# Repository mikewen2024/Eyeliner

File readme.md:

# Eyeliner — Melty-Brain Combat Robot

A 1lb (antweight) melty-brain combat robot. A melty-brain spins the entire chassis at 1,000–2,000 RPM while pulsing drive motors ~100 times/second to achieve controlled translational movement — maximum hitting power, and one of the hardest archetypes to execute correctly.

**Key system requirements:** MHz-range onboard MCU, high-range accelerometer (~400g) for RPM/heading, per-motor drive current of ~30A (≈500W), and all electronics surviving constant 200–300g with peak impact accelerations orders of magnitude higher.

To read more about the development of the project and past versions, check out my personal technical blog [here](https://future-wool-0d5.notion.site/Eyeliner-Melty-brain-Combat-Robot-2ede4d628bf380b29920f43a3518d5c0) :)

---

## Current Iteration

**Hardware:** XIAO ESP32-S3 PLUS MCU, LSM6DSV320X IMU, Repeat Robotics BEC, ELRS nano receiver, dual 35A ESCs, ws2812b LED strip, Standalone ADXL-375 Accelerometer

**Key Features:**

- Extensive consideration for signal integrity, decoupling and bulk capacitance, and transients protection on all vulnerable MCU GPIO ports
- Made to run on 4s-6s LiHV with minimal changes (TVS diode change), interface with a range of possible sensors, and run interchangeably with antweight and beetleweight electronics
- Interchangeable high-kv 2207 "pacer" motors (outright top-range hitting power) and low-kv 2822 motors (faster spin-up with less current draw)
- LSM6DSV320X IMU with high and low range readout registers, built-in impact detection and interrupt capability, SPI interface 
- Custom UART interface for ELRS receiver to improve signal stability and expand channel bandwidth to 16 channels 
- LED strips for better heading and state indication
- Spare set of SPI connections for standalone ADXL375 or other sensors
- Shock isolated mounting with bracing for connectors
- Judicious ground plane placement for good return paths and receiver signal integrity, high-speed trace routing to reduce cross-talk and RC-loss, balancing current surge protection and voltage surge protection with TVS Diodes
- Up to 2500W burst capacity on HV side via solder busses, structural stability via extensive via stitching
- Spare GPIO connections for thermistors, IR sensors, etc...
- DSHOT600 and DSHOT1200 for high rate and accurate motor torque control at speed, built-in twisted-pairs for signal lines with GND return paths as close as possible to ESC grounds

**Upcoming Changes:** 

- Dual H3LIS331DL accelerometers (rotational speed without knowing center of rotation), easier-to-solder footprint
- More robust LDO system for 5V side
- Precharge circuit for higher-voltage inputs
- Two-way DSHOT for traction control
- Easily-removable high-speed connectors for ESCs
- Switch to STM32 for higher clock speeds, ESP32 for telemetry and LED control only
- Custom sensored ESCs
- Custom BMS

---

### Byeliner — Beetleweight Upscale V0 *(March 2026 – Present)*
**Class:** 3lb (beetleweight)
**Hardware Changes:** Oversize 790 kV 3548 motors, dual 80A 8s-capable VORTEX F65 ESCs, dual 4s LiHV batteries

A 3lb version ("Byeliner") built for **Robobrawl**, early April 2026. The chassis is a rigid CURV and aluminum skeleton wrapped in TPU. On the code side, we are also moving towards platformIO for more organized operation.

---

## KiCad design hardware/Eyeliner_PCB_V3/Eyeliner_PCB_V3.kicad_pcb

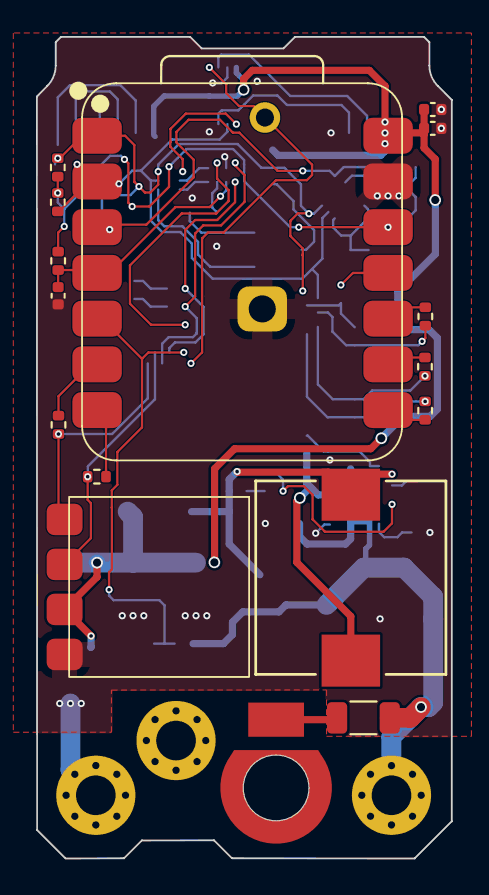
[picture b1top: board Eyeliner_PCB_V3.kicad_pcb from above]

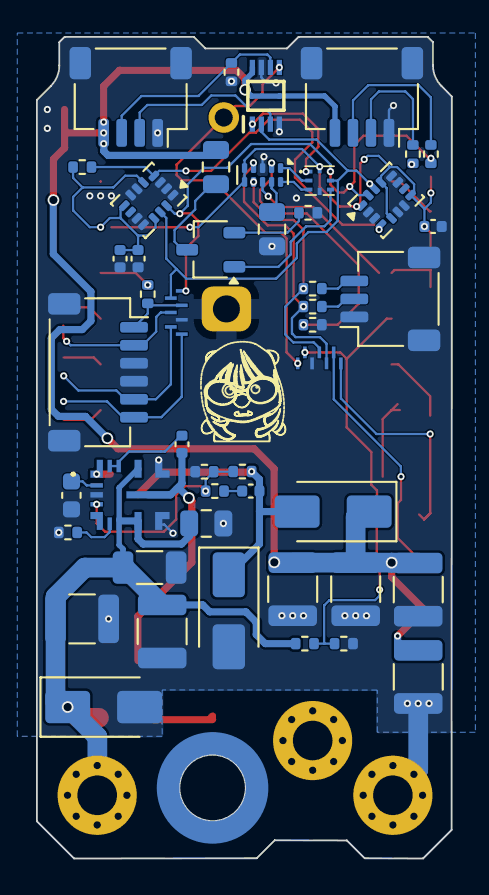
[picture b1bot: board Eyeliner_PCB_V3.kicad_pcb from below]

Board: 2 copper layers, 23.0 x 45.6 mm, 67 parts (47 on the bottom side), 48 nets.

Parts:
Batt1: VBat; MountingHole_2.2mm_M2_Pad_Via
C1: C0603X5R500-105KNP-CT; C_0603_1608Metric
C2: GMC21X7R104K35NT; C_0805_2012Metric
C3, C5, C11, C12, C16, C17: MSASG32MSB5226MPNA01; C_1210_3225Metric
C4: GCJ31CR71H225KA12L; C_1206_3216Metric
C6: 470nF; C_0402_1005Metric
C7, C9: 100nF; C_0402_1005Metric
C8, C14, C15: 100 nF; C_0402_1005Metric
C10: 16pF; C_0402_1005Metric
C13: 1uF; C_0402_1005Metric
Conn_LEDs1: JST_SH_01x04; JST_SH_SM04B-SRSS-TB_1x04-1MP_P1.00mm_Horizontal
D1: SMAJ30A or SMAJ24A; D_SMA
D2: SMAJ6.0A; D_SMA
D3: STPS2L30A; D_SMA
ESCs1: JST_SH_01x06; JST_SH_SM06B-SRSS-TB_1x06-1MP_P1.00mm_Horizontal
GND1: GND_ESCs; MountingHole_2.2mm_M2_Pad_Via
HV1: HV_ESCs; MountingHole_2.2mm_M2_Pad_Via
I2C1: JST_SH_01x04; JST_SH_SM04B-SRSS-TB_1x04-1MP_P1.00mm_Horizontal
IC1: PCA9570GMH
IC2: 74AHCT2G125DC,125; SOP50P310X100-8N
IR1: TestPoint_2Pole; C_0805_2012Metric
J1: S7131-45R; HARWIN_S7121-42R
J2: 4871; 4871_Switch_Precharge
L1: SRP1038A-150M; IND_SRP1038A_BRN
Q1: BSS138; TSOT-23
R1, R19: 4.7k; R_0402_1005Metric
R2, R3, R5, R15, R16, R17, R18, R20, R21, R22, R23: 100; R_0402_1005Metric
R4: 30k; R_0402_1005Metric
R6: RC1206FR-07100RL; R_1206_3216Metric
R7, R11: 20k; R_0402_1005Metric
R8: 5.1k; R_0402_1005Metric
R9, R10, R13, R14: 1k; R_0402_1005Metric
R12: 2k; R_0402_1005Metric
R24: 10k; R_0402_1005Metric
RTD_Onboard1: TestPoint_2Pole; C_0805_2012Metric
Receiver1: BetaFPV ELRS Lite
Temps1: JST_SH_01x03; JST_SH_SM03B-SRSS-TB_1x03-1MP_P1.00mm_Horizontal
U1: LM61440AANRJRR; LM61440AASQRJRRQ1
U2: XIAO-ESP32-S3-SMD
U3, U4: LSM6DSV320XTR; LGA-14_3x2.5mm_P0.5mm_LayoutBorder3x4y
U5: TMUX1204DQAR; USON-10_2.5x1.0mm_P0.5mm
U6, U7: RCLAMP3346P.TNT; SGP2708N7_SEM

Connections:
/Top_Board/Bias: C10.1, D2.1 (K), D3.2 (A), L1.2, R7.2, U1.1 (BIAS_1), U1.15 (BIAS_2)
/Top_Board/Dshot1: R23.2, U2.9 (D8)
/Top_Board/Dshot1_Proc: ESCs1.5, R23.1, U7.7
/Top_Board/Dshot2: R21.2, U2.10 (D9)
/Top_Board/Dshot2_Proc: ESCs1.2, R21.1, U7.6
/Top_Board/ESC_Telem1: R22.2, U2.8 (D7)
/Top_Board/ESC_Telem1_Proc: ESCs1.6, R22.1, U7.1
/Top_Board/ESC_Telem2: R20.2, U2.11 (D10)
/Top_Board/ESC_Telem2_Proc: ESCs1.1, R20.1, U7.3
/Top_Board/FB: R7.1, R8.2, R9.2, U1.4 (FB)
/Top_Board/INT: R1.1, U2.3 (D2), U3.4 (INT1), U4.4 (INT1)
/Top_Board/LEDs: IC2.5 (2A), U2.16 (MTDO), U6.1
/Top_Board/LEDs_EN: IC1.1 (P0), IC2.1 (~1OE)
/Top_Board/NC_1: U1.5 (PGOOD_1), U1.16 (PGOOD_2)
/Top_Board/Receiver_RX: R3.1, Receiver1.1 (RX), U6.4
/Top_Board/Receiver_TX: R2.2, Receiver1.2 (TX), U6.5
/Top_Board/SCL: IC1.6 (SCL), IC2.2 (1A), R10.1, R15.1, U2.2 (D1), U3.13 (SCL), U4.13 (SCL), U7.5
/Top_Board/SDA: IC1.7 (SDA), R13.1, R16.2, U2.1 (D0), U3.14 (SDA), U4.14 (SDA), U7.4
/Top_Board/Sense: C15.1, R14.1, U2.4 (D3), U5.8 (D)
/Top_Board/Temp1_1: R18.2, U5.7 (S4), U6.6
/Top_Board/Temp2_1: R17.2, U5.4 (S3), U6.3
/Top_Board/TempRef_1: R19.2, U5.2 (S1)
/Top_Board/Temp_Sel1: IC1.2 (P1), U5.1 (A0)
/Top_Board/Temp_Sel2: IC1.3 (P2), U5.10 (A1)
/Top_Board/Vbat_Sense: R11.1, R12.2, U2.5 (D4), U6.7
GND: C1.1, C2.2, C3.2, C4.2, C5.2, C6.2, C8.2, C9.2, C11.2, C12.2, C13.2, C14.2, C15.2, C16.2, C17.2, Conn_LEDs1.1, Conn_LEDs1.MP, D1.2 (A), D2.2 (A), ESCs1.3, ESCs1.4, ESCs1.MP, GND1.1 (1_1), I2C1.1, I2C1.MP, IC1.4 (VSS), IC2.4 (GND), IC2.7 (~2OE), R4.1, R5.1, R8.1, R12.1, R19.1, R24.1, RTD_Onboard1.2, Receiver1.4 (GND), Temps1.1, Temps1.MP, U1.3 (AGND), U1.9 (PGND1_1), U1.11 (PGND2_1), U1.17 (PGND1_2), U1.18 (PGND2_2), U2.13 (GND), U2.25 (PAD), U3.2 (SDX), U3.3 (SCX), U3.6 (GND), U3.7 (GND), U3.10 (OCS_AUX), U3.11 (SDO_AUX), U4.1 (SDO/TA0), U4.2 (SDX), U4.3 (SCX), U4.6 (GND), U4.7 (GND), U4.10 (OCS_AUX), U4.11 (SDO_AUX), U5.3 (GND), U6.2, U7.2
unnamed: C10.2, R9.1
unnamed: Conn_LEDs1.2, IC2.3 (2Y)
unnamed: Conn_LEDs1.3, IC2.6 (1Y), R24.2
unnamed: I2C1.2, R15.2
unnamed: I2C1.3, R16.1
unnamed: IC1.5 (P3), Q1.1 (G)
unnamed: J1.SH1 (SHIELD_SH1), R6.2
unnamed: Batt1.1 (1_1), J2.2 (Ext)
unnamed: IR1.2, Q1.3 (D)
unnamed: Q1.2 (S), R5.2
unnamed: R17.1, Temps1.2
unnamed: R18.1, Temps1.3
unnamed: C7.2, U1.13 (RBOOT), U1.14 (CBOOT)
unnamed: R4.2, U1.6 (RT)
unnamed: C7.1, L1.1, U1.10 (SW)
unnamed: C1.2, U1.2 (VCC)
unnamed: R3.2, U2.6 (D5)
unnamed: R2.1, U2.7 (D6)
unnamed: RTD_Onboard1.1, U5.9 (S2)
VCC_3V3: C6.1, C8.1, C9.1, IC1.8 (VDD), R1.2, R10.2, R13.2, R14.2, U2.12 (3V3_OUT), U3.1 (SDO/TA0), U3.5 (VDDIO), U3.8 (VDD), U3.12 (CS), U4.5 (VDDIO), U4.8 (VDD), U4.12 (CS), U5.5 (EN), U5.6 (VDD)
VCC_5V: C11.1, C12.1, C13.1, C14.1, C16.1, C17.1, Conn_LEDs1.4, D3.1 (K), I2C1.4, IC2.8 (VCC), IR1.1, Receiver1.3 (5V), U2.14 (VBUS)
VCC_HV: C2.1, C3.1, C4.1, C5.1, D1.1 (K), HV1.1 (1_1), J2.1 (In), R6.1, R11.2, U1.7 (EN/SYNC), U1.8 (VIN1), U1.12 (VIN2)

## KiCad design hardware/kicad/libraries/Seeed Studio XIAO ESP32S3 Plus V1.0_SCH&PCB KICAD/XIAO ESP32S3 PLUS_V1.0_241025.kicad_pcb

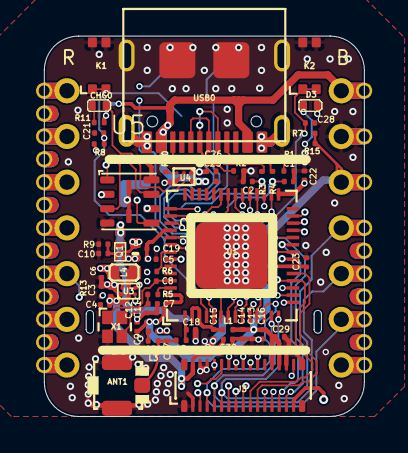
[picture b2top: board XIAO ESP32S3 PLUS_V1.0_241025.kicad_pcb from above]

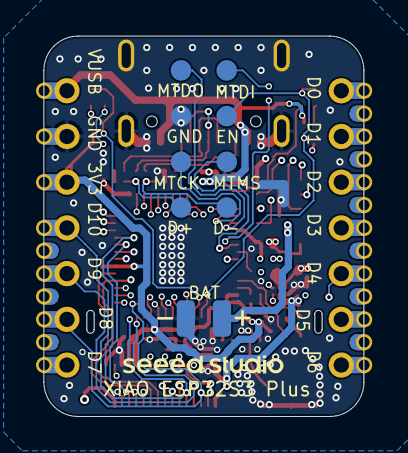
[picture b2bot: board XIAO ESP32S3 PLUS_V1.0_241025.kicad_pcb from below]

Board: 6 copper layers, 17.8 x 21.1 mm, 70 parts (10 on the bottom side), 62 nets.

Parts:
ANT1: U.FL-R-SMT-1; U-FL3P-SMD-2.6X2.6X1.0MM
BAT0: VBAT; TP-80X40MIL
C1, C2, C17, C20: DNP; C0201
C3, C9, C13, C16: 2.2uF; C0201
C4, C5, C6: 4.7uF; C0201
C7, C8, C28: 10pF; C0201
C10, C21, C25, C26: 1uF; C0201
C11, C14, C15, C19, C22, C23, C29, C30: 100nF; C0201
C12: 10nF; C0201
C18: 1pF; C0201
CHG0: RED; LED-0402
D2: LMBR4010BST5G; DFN1006-2L
D3: Yellow; LED-0402
GND0: GND; TP-80X40MIL
J3: DF40C-30DP-0.4V(51); BTB30-0.4-7.52X2.97X1.14
K1, K2: SKTAAAE010/311021459; SW4-SMD-2.8-2.6X1.6X0.53MM
L1: 2nH; L0201
L2: 3.3nH; L0201
L3: DNP; L0201
L4: 470nH; L0603
Q1: PMOS_1.00.60.35MM; PMOS_1.0*0.6*0.35MM
R1, R2: 5.1K; R0201
R3, R4: 22R; R0201
R5: 0R; R0201
R6: 499R; R0201
R7, R8, R11: 10K; R0201
R9: 100K; C0201
R10: 220K; R0201
R13: 249K; R0201
R15: 1.5K; R0201
TP1, TP2, TP3, TP4, TP5, TP6, TP7, TP8: TEST-POINT'4545'; TP-D45MIL
U1: MCU-ESP32-S3; QFN56G-0.4-7X7MM
U2: XIAO-HALF-HOLE-23P; MOUDLE23P-XIAO-HALF-HOLE
U3: PMIC-SGM6029; BGA6-0.35-0.745X10.95X0.4MM
U4: SGM40567-4.2XG/TR; WLCSP-0.4-0.92X1.16X0.4MM
U5: PY25Q128HA-DFH-IR; USON8-0.8-3X3X0.55MM
USB0: UBF31-0171; USB2.0-TYPE-C
X1: 40MHz/306011364; X4-SMD-1.6X1.2X0.35MM

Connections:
/D0/A0: U1.6 (GPIO1), U2.1 (PA02_A0_D0)
/D1/A1: U1.7 (GPIO2), U2.2 (PA4_A1_D1)
/D2/A2: J3.2, U1.8 (GPIO3), U2.3 (PA10_A2_D2)
/D3/A3: U1.9 (GPIO4), U2.4 (PA11_A3_D3)
/D4/I2C_SDA: U1.10 (GPIO5), U2.5 (PA8_A4_D4_SDA)
/D5/I2C_SCL: U1.11 (GPIO6), U2.6 (PA9_A5_D5_SCL)
/D6/TX: R6.2, U2.7 (PB08_A6_D6_TX)
/D7/RX: U1.50 (U0RXD), U2.8 (PB09_A7_D7_RX)
/D8/A8/SCK: J3.3, U1.12 (GPIO7), U2.9 (PA7_A8_D8_SCK)
/D9/A9/MISO: J3.4, U1.13 (GPIO8), U2.10 (PA5_A9_D9_MISO)
/D10/A10/MOSI: J3.5, U1.14 (GPIO9), U2.11 (PA6_A10_D10_MOSI)
/EN: C21.2, K1.1 (A0), K1.3 (A1), R8.1, TP6.T, U1.4 (CHIP_PU)
/ESP_USB_D+: C1.2, R4.2, TP8.T, U1.26 (GPIO20)
/ESP_USB_D-: C2.2, R3.2, TP7.T, U1.25 (GPIO19)
/GPIO0: C28.2, K2.1 (A0), K2.3 (A1), R7.1, U1.5 (GPIO0)
/IO10/XMCLK/ADC_BAT: J3.6, U1.15 (GPIO10), U2.20
/IO11/DVP_Y8/SPI_MOSI1: J3.7, U1.16 (GPIO11), U2.21
/IO12/DVP_Y7/SPI_MISO1: J3.8, U1.17 (GPIO12), U2.22
/IO13/DVP_PCLK/SPI_SCK1: J3.9, U1.18 (GPIO13), U2.23
/IO14/DVP_Y6: J3.10, U1.19 (GPIO14)
/IO15/DVP_Y2: J3.11, U1.21 (XTAL_32K_P)
/IO16/DVP_Y5: J3.12, U1.22 (XTAL_32K_N)
/IO17/DVP_Y3: J3.13, U1.23 (GPIO17)
/IO18/DVP_Y4: J3.14, U1.24 (GPIO18)
/IO21/USER_LED: D3.-, J3.16, U1.27 (GPIO21)
/IO38/DVP_VSYNC/I2S_SD: J3.23, U1.43 (GPIO38), U2.15
/IO47/DVP_HREF: J3.22, U1.37 (SPICLK_P)
/IO48/DVP_Y9: J3.21, U1.36 (SPICLK_N)
/MTCK/IO39/CAM_SCL/I2S_SCK: J3.24, TP5.T, U1.44 (MTCK), U2.16
/MTDI/IO41/PDM_DATA/RX1: J3.26, TP3.T, U1.47 (MTDI), U2.18
/MTDO/IO40/CAM_SDA/I2S_WS: J3.25, TP4.T, U1.45 (MTDO), U2.17
/MTMS/IO42/PDM_CLK/TX1: J3.27, TP2.T, U1.48 (MTMS), U2.19
/SPICLK: U1.33 (SPICLK), U5.6 (SCLK)
/SPICS0: U1.32 (SPICS0), U5.1 (CS#)
/SPID: U1.35 (SPID), U5.5 (SI)
/SPIHD: U1.30 (SPIHD), U5.7 (HOLD#/RESET#)
/SPIQ: U1.34 (SPIQ), U5.2 (SO)
/SPIWP: U1.31 (SPIWP), U5.3 (WP#)
/USB_D+: R4.1, USB0.A6 (A6/DP1), USB0.B6 (B6/DP2)
/USB_D-: R3.1, USB0.A7 (A7/DN1), USB0.B7 (B7/DN2)
/VBAT: BAT0.1 (T), C26.1, Q1.1 (D), U4.A1 (BAT)
/VBUS: C10.1, C25.1, D2.+, Q1.2 (G), R9.2, R11.1, U2.14 (5V), U4.A2 (VIN), USB0.A4_B9 (A4/B9/VBUS), USB0.B4_A9 (B4/A9/VBUS)
/VCC_3V3: C5.2, C6.2, C9.2, C11.2, C12.2, C13.2, C14.2, C16.2, C19.2, C23.1, C29.2, J3.18, J3.19, L1.1, L4.2, R7.2, R8.2, R15.2, U1.20 (VDD3P3_RTC), U1.46 (VDD3P3_CPU), U1.55 (VDDA@1), U1.56 (VDDA@2), U2.12 (3V3), U3.A2 (VOS)
/VDD_SPI: C22.2, U1.29 (VDD_SPI), U5.8 (VCC)
/VIN: C3.1, C4.1, C30.2, D2.-, J3.15, J3.30, Q1.3 (S), U3.B1 (VIN), U3.C2 (EN)
GND_POWER: ANT1.GND1, ANT1.GND2, C1.1, C2.1, C3.2, C4.2, C5.1, C6.1, C7.2, C8.1, C9.1, C10.2, C11.1, C12.1, C13.1, C14.1, C15.1, C16.1, C17.1, C18.1, C19.1, C20.1, C21.1, C22.1, C23.2, C25.2, C26.2, C28.1, C29.1, C30.1, GND0.1 (T), J3.1, J3.17, J3.28, J3.29, J3.31, J3.33, J3.34, K1.2 (B0), K1.4 (B1), K2.2 (B0), K2.4 (B1), R1.1, R2.2, R9.1, R10.1, R13.1, TP1.T, U1.57 (GND), U2.13 (GND), U3.A1 (GND), U4.B1 (F), U4.C2 (GND), U5.4 (GND), U5.9 (GND), U5.10 (GND), USB0.A1_B12 (A1/B12/GND), USB0.B1_A12 (B1/A12/GND), USB0.S1, USB0.S2, USB0.S3, USB0.S4, USB0.S5 (S1), USB0.S6 (S2), X1.2 (GND), X1.4 (GND@1)
unnamed: ANT1.D, C17.2, L2.1, L3.2
unnamed: C20.2, L3.1
unnamed: CHG0.+, R11.2
unnamed: D3.+, R15.1
unnamed: C18.2, L2.2, U1.1 (LNA_IN)
unnamed: R6.1, U1.49 (U0TXD)
unnamed: C15.2, L1.2, U1.2 (VDD3P3@1), U1.3 (VDD3P3@2)
unnamed: C8.2, U1.53 (XTAL_N), X1.1 (X1)
unnamed: R5.1, U1.54 (XTAL_P)
unnamed: R13.2, U3.C1 (MODE)
unnamed: L4.1, U3.B2 (SW)
unnamed: R10.2, U4.C1 (IREF)
unnamed: CHG0.-, U4.B2 (NCHG)
unnamed: R1.2, USB0.A5 (A5/CC1)
unnamed: R2.1, USB0.B5 (B5/CC2)
unnamed: C7.1, R5.2, X1.3 (X2)

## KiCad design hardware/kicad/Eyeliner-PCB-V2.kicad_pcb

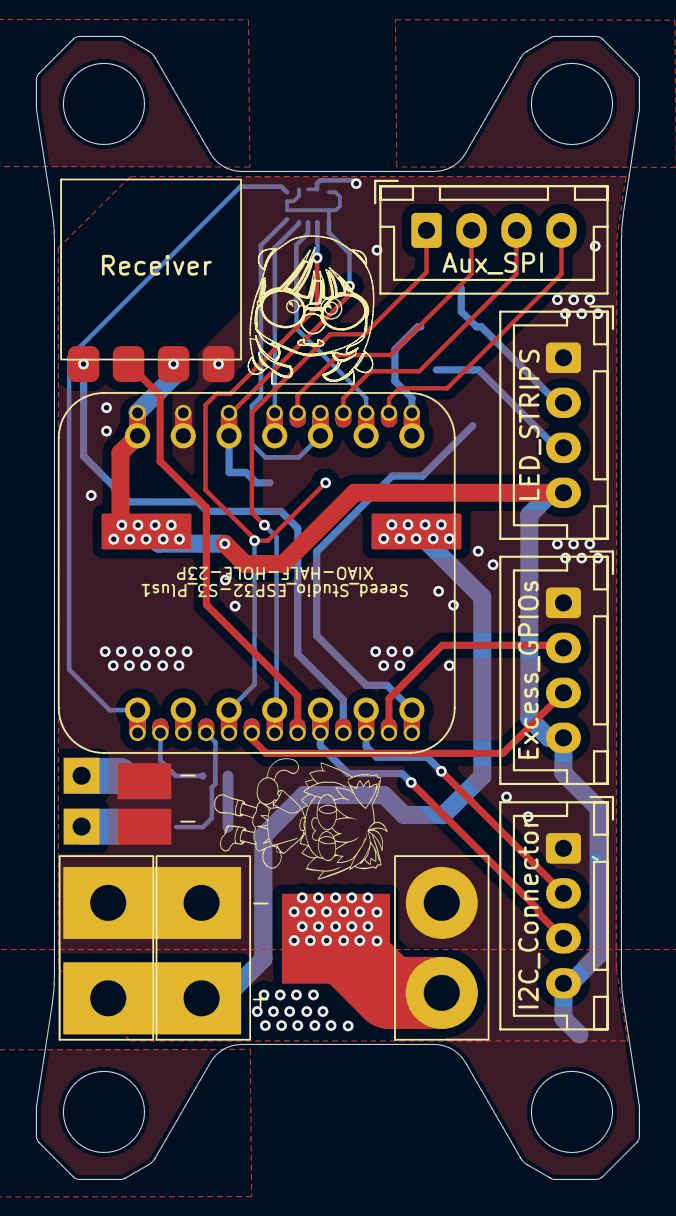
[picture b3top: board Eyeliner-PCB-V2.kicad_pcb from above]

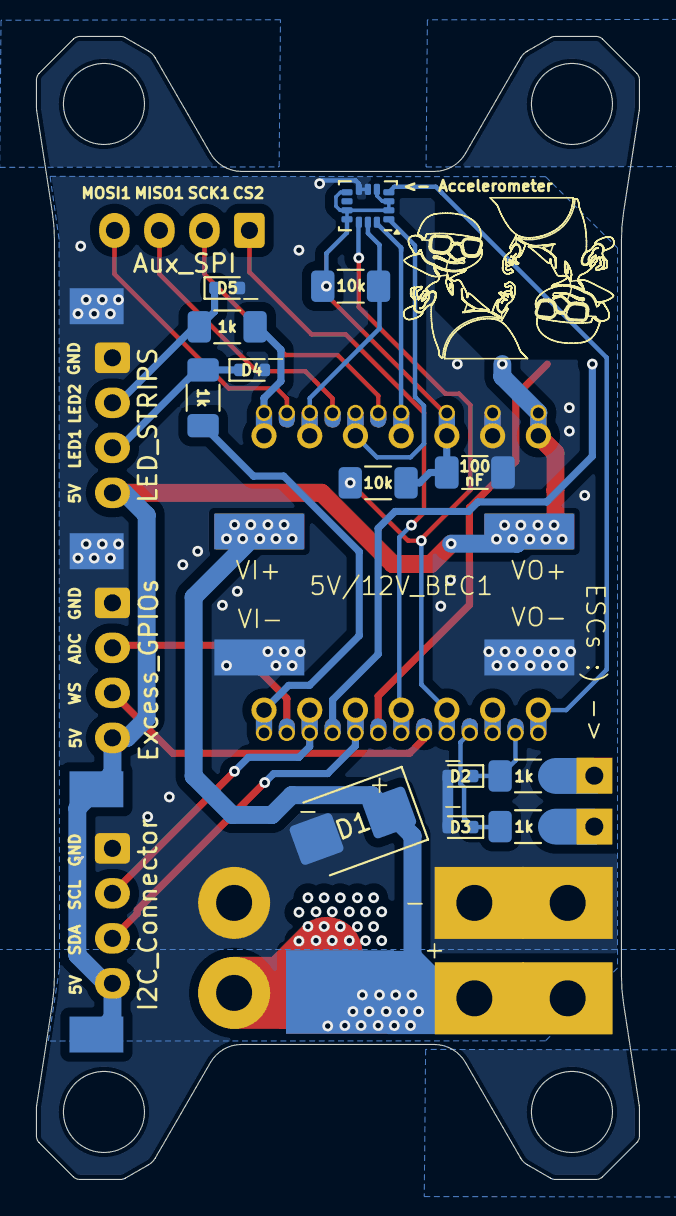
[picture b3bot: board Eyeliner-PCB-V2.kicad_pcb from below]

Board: 2 copper layers, 33.5 x 63.5 mm, 32 parts (17 on the bottom side), 28 nets.

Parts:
1k, 1k#2, 1k#3, 1k#4: 1k; R_1206_3216Metric_Pad1.30x1.75mm_HandSolder
5V/12V_BEC1: BEC_5V_12V
10k, 10k#2: 10k; R_1206_3216Metric_Pad1.30x1.75mm_HandSolder
100: 100 nF; C_1206_3216Metric_Pad1.33x1.80mm_HandSolder
+: XT-30_VERT
<- Accelerometer: LSM6DSV320XTR; LGA-14_3x2.5mm_P0.5mm_LayoutBorder3x4y
D1: D_TVS; D_SMB
D2, D3: D_TVS; D_SOD-523
D4: D_LED_1; D_SOD-523
D5: D_LED_2; D_SOD-523
ESC1, ESC2: ESC-PWM-Connection
Fingertech_Switch1: Fingertech_Switch
J1: LED_STRIPS; JST_XH_B4B-XH-A_1x04_P2.50mm_Vertical
J2: Aux_SPI; JST_XH_B4B-XH-A_1x04_P2.50mm_Vertical
J3: I2C_Connector; JST_XH_B4B-XH-A_1x04_P2.50mm_Vertical
J4: Excess_GPIOs; JST_XH_B4B-XH-A_1x04_P2.50mm_Vertical
Receiver: BetaFPV ELRS Lite
Seeed_Studio_ESP32-S3_Plus1: XIAO-HALF-HOLE-23P; MOUDLE23P-SMD-2.54-21X17.8MM.kicad_mod.kicad_sym
U1, U2, U3, U4, U5, U6: Generic_SMD_THT
XT-30_VERT1, XT-30_VERT3: XT-30_VERT

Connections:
4S_VCC: 5V/12V_BEC1.VIN+, +.VCC, D1.1 (K), Fingertech_Switch1.OUT, XT-30_VERT1.VCC
ADC_BAT: J4.2, Seeed_Studio_ESP32-S3_Plus1.20 (GPIO10_XMCLK/ADC_BAT)
CS_1: 10k.2, <- Accelerometer.12 (CS), Seeed_Studio_ESP32-S3_Plus1.3 (GPIO3_D2/A2)
CS_2: J2.1, Seeed_Studio_ESP32-S3_Plus1.4 (GPIO4_D3/A3)
ESC_1: 1k#3.2, D2.1 (K), Seeed_Studio_ESP32-S3_Plus1.15 (GPIO38_DVP_VSYNC/I2S_SD)
ESC_2: 1k.2, D3.1 (K), Seeed_Studio_ESP32-S3_Plus1.16 (GPIO39_CAM_SCL/I2S_SCK)
GND: 5V/12V_BEC1.VIN-, 5V/12V_BEC1.VO-, 100.2, +.GND, <- Accelerometer.6 (GND), <- Accelerometer.7 (GND), D1.2 (A), D2.2 (A), D3.2 (A), D4.2 (A), D5.2 (A), J1.1, J3.1, J4.1, Receiver.4 (GND), Seeed_Studio_ESP32-S3_Plus1.13 (GND), U1.1 (GND), U2.1 (GND), U3.1 (GND), U5.1 (GND), XT-30_VERT1.GND, XT-30_VERT3.GND
INT_1: <- Accelerometer.4 (INT1), Seeed_Studio_ESP32-S3_Plus1.1 (GPIO1_D0/A0)
LED_1: 1k#4.2, Seeed_Studio_ESP32-S3_Plus1.7 (U0TXD_D6/TX)
LED_2: 1k#2.2, Seeed_Studio_ESP32-S3_Plus1.8 (U0RXD_D7/RX)
MISO: <- Accelerometer.1 (SDO/TA0), Seeed_Studio_ESP32-S3_Plus1.10 (GPIO8_D9/A9/MISO)
MISO1: J2.3, Seeed_Studio_ESP32-S3_Plus1.22 (GPIO12_DVP_Y7/SPI_MISO1)
MOSI: <- Accelerometer.14 (SDA), Seeed_Studio_ESP32-S3_Plus1.11 (GPIO9_D10/A10/MOSI)
MOSI1: J2.4, Seeed_Studio_ESP32-S3_Plus1.21 (GPIO11_DVP_Y8/SPI_MOSI1)
unnamed: 1k#4.1, D4.1 (K), J1.3
unnamed: 1k#2.1, D5.1 (K), J1.2
unnamed: 1k#3.1, ESC1.1 (PWM)
unnamed: 1k.1, ESC2.1 (PWM)
Receiver_RX: Receiver.1 (RX), Seeed_Studio_ESP32-S3_Plus1.19 (GPIO42_PDM_CLK/TX1)
Receiver_TX: Receiver.2 (TX), Seeed_Studio_ESP32-S3_Plus1.18 (GPIO41_PDM_DATA/RX1)
SCK: 10k#2.2, <- Accelerometer.13 (SCL), Seeed_Studio_ESP32-S3_Plus1.9 (GPIO7_D8/A8/SCK)
SCK1: J2.2, Seeed_Studio_ESP32-S3_Plus1.23 (GPIO13_DVP_PCLK/SPI_SCK1)
SCL: J3.2, Seeed_Studio_ESP32-S3_Plus1.6 (GPIO6_D5/A5/I2C_SCL)
SDA: J3.3, Seeed_Studio_ESP32-S3_Plus1.5 (GPIO5_D4/A4/I2C_SDA)
SWITCH INPUT: Fingertech_Switch1.IN, XT-30_VERT3.VCC
VCC 3V3: 10k.1, 10k#2.1, 100.1, <- Accelerometer.2 (SDX), <- Accelerometer.3 (SCX), <- Accelerometer.5 (VDDIO), <- Accelerometer.8 (VDD), <- Accelerometer.10 (OCS_AUX), <- Accelerometer.11 (SDO_AUX), Seeed_Studio_ESP32-S3_Plus1.12 (VCC_3V3)
VCC 5V: 5V/12V_BEC1.VO+, J1.4, J3.4, J4.4, Receiver.3 (5V), Seeed_Studio_ESP32-S3_Plus1.14 (VBUS), U4.1 (VCC), U6.1 (VCC)
WS: J4.3, Seeed_Studio_ESP32-S3_Plus1.17 (GPIO40_CAM_SDA/I2S_WS)

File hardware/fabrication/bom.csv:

Designator,Footprint,Quantity,Value,LCSC Part #
"+, XT-30_VERT1, XT-30_VERT3",XT-30_VERT,3,~,
100,1206,1,100 nF,
"10K, 1K",1206,2,10k,
"1K_5, 1K_4, 1K_3, 1K_2",1206,4,1k,
5V/12V_BEC1,BEC_5V_12V,1,~,
<- ACCELEROMETER,LGA-14_3x2.5mm_P0.5mm_LayoutBorder3x4y,1,LSM6DSV320XTR,
D1,D_SMB,1,D_TVS,
"D2, D3",D_SOD-523,2,D_TVS,
D4,D_SOD-523,1,D_LED_1,
D5,D_SOD-523,1,D_LED_2,
"ESC1, ESC2",ESC-PWM-Connection,2,~,
FINGERTECH_SWITCH1,Fingertech_Switch,1,~,
J1,JST_XH_B4B-XH-A_1x04_P2.50mm_Vertical,1,LED_STRIPS,
J2,JST_XH_B4B-XH-A_1x04_P2.50mm_Vertical,1,Aux_SPI,
J3,JST_XH_B4B-XH-A_1x04_P2.50mm_Vertical,1,I2C_Connector,
J4,JST_XH_B4B-XH-A_1x04_P2.50mm_Vertical,1,Excess_GPIOs,
RECEIVER,BetaFPV ELRS Lite,1,~,
SEEED_STUDIO_ESP32-S3_PLUS1,MOUDLE23P-SMD-2.54-21X17.8MM.kicad_mod.kicad_sym,1,XIAO-HALF-HOLE-23P,
"U1, U2, U3, U4, U5, U6",Generic_SMD_THT,6,~,

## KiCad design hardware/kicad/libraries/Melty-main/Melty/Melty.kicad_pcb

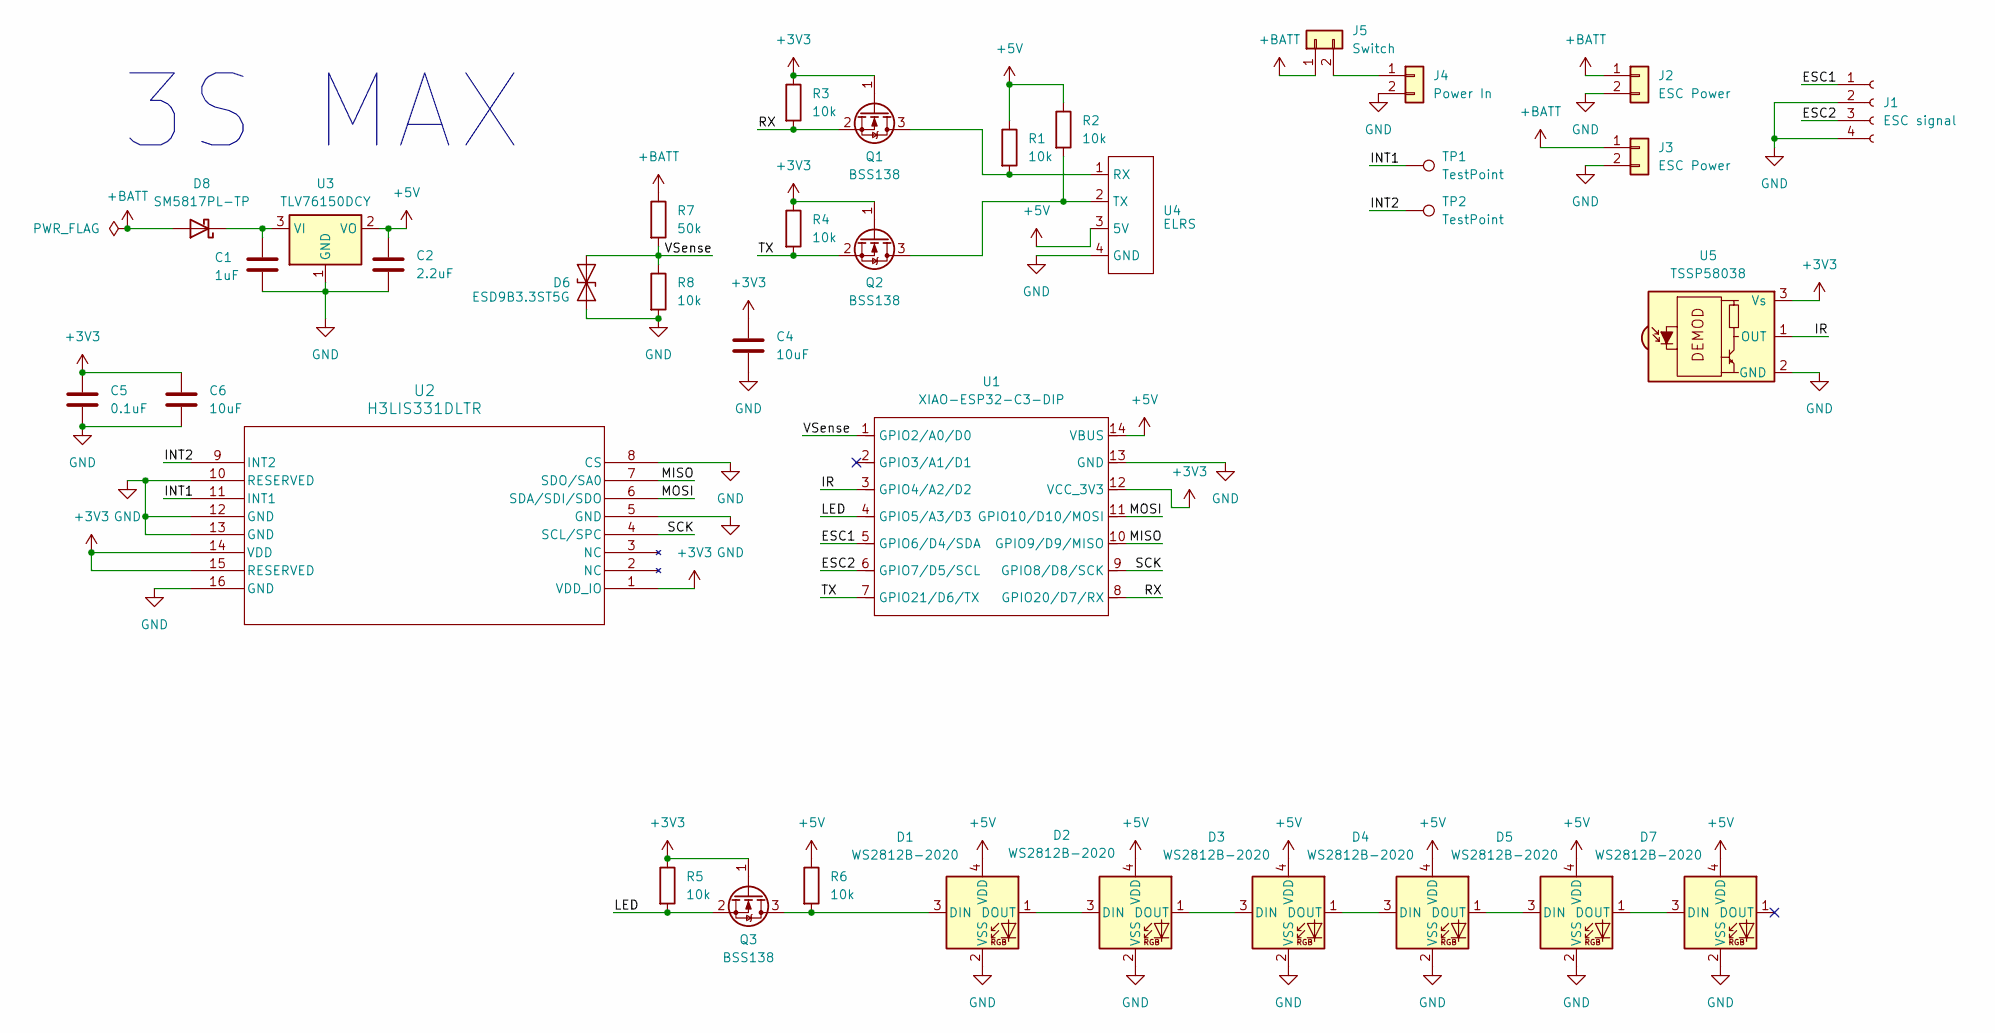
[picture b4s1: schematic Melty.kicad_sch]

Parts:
C1: 1uF; C_0603_1608Metric_Pad1.08x0.95mm_HandSolder
C2: 2.2uF; C_0603_1608Metric_Pad1.08x0.95mm_HandSolder
C4, C6: 10uF; C_0603_1608Metric_Pad1.08x0.95mm_HandSolder
C5: 0.1uF; C_0603_1608Metric_Pad1.08x0.95mm_HandSolder
D1, D2, D3, D4, D5, D7: WS2812B-2020; LED_WS2812B-2020_PLCC4_2.0x2.0mm
D6: ESD9B3.3ST5G; D_SOD-923
D8: SM5817PL-TP
J1: ESC signal; JST_GH_SM04B-GHS-TB_1x04-1MP_P1.25mm_Horizontal
J2, J3: ESC Power; PowerPADS
J4: Power In; AMASS_XT30UPB-M_1x02_P5.0mm_Vertical
J5: Switch; SwitchPads
Q1, Q2, Q3: BSS138; SOT-23
R1, R2, R3, R4, R5, R6, R8: 10k; C_0603_1608Metric_Pad1.08x0.95mm_HandSolder
R7: 50k; C_0603_1608Metric_Pad1.08x0.95mm_HandSolder
TP1, TP2: TestPoint; TestPoint_Pad_D1.0mm
U1: XIAO-ESP32-C3-DIP; XIAO-ESP32S3-SMD
U2: H3LIS331DLTR; QFN_31DLTR_STM
U3: TLV76150DCY; SOT-223-3_TabPin2
U4: ELRS; BetaFPV ELRS Lite
U5: TSSP58038; Vishay_MINICAST-3Pin

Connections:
+3V3: C4.1, C5.1, C6.1, Q1.1 (G), Q2.1 (G), Q3.1 (G), R3.1, R4.1, R5.1, U1.12 (VCC_3V3), U2.1 (VDD_IO), U2.14 (VDD), U2.15 (RESERVED), U5.3 (Vs)
+5V: C2.1, D1.4 (VDD), D2.4 (VDD), D3.4 (VDD), D4.4 (VDD), D5.4 (VDD), D7.4 (VDD), R1.1, R2.1, R6.1, U1.14 (VBUS), U3.2 (VO), U4.3 (5V)
/ESC1: J1.1, U1.5 (GPIO6/D4/SDA)
/ESC2: J1.3, U1.6 (GPIO7/D5/SCL)
/INT1: TP1.1, U2.11 (INT1)
/INT2: TP2.1, U2.9 (INT2)
/IR: U1.3 (GPIO4/A2/D2), U5.1 (OUT)
/LED: Q3.2 (S), R5.2, U1.4 (GPIO5/A3/D3)
/MISO: U1.10 (GPIO9/D9/MISO), U2.7 (SDO/SA0)
/MOSI: U1.11 (GPIO10/D10/MOSI), U2.6 (SDA/SDI/SDO)
/RX: Q1.2 (S), R3.2, U1.8 (GPIO20/D7/RX)
/SCK: U1.9 (GPIO8/D8/SCK), U2.4 (SCL/SPC)
/TX: Q2.2 (S), R4.2, U1.7 (GPIO21/D6/TX)
/VSense: D6.1 (A1), R7.2, R8.1, U1.1 (GPIO2/A0/D0)
GND: C1.2, C2.2, C4.2, C5.2, C6.2, D1.2 (VSS), D2.2 (VSS), D3.2 (VSS), D4.2 (VSS), D5.2 (VSS), D6.2 (A2), D7.2 (VSS), J1.2, J1.4, J2.2, J3.2, J4.2, R8.2, U1.13 (GND), U2.5 (GND), U2.8 (CS), U2.10 (RESERVED), U2.12 (GND), U2.13 (GND), U2.16 (GND), U3.1 (GND), U4.4 (GND), U5.2 (GND)
unnamed: D1.3 (DIN), Q3.3 (D), R6.2
unnamed: D1.1 (DOUT), D2.3 (DIN)
unnamed: D2.1 (DOUT), D3.3 (DIN)
unnamed: D3.1 (DOUT), D4.3 (DIN)
unnamed: D4.1 (DOUT), D5.3 (DIN)
unnamed: D5.1 (DOUT), D7.3 (DIN)
unnamed: J4.1, J5.2
unnamed: Q1.3 (D), R1.2, U4.1 (RX)
unnamed: Q2.3 (D), R2.2, U4.2 (TX)

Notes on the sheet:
3S MAX

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
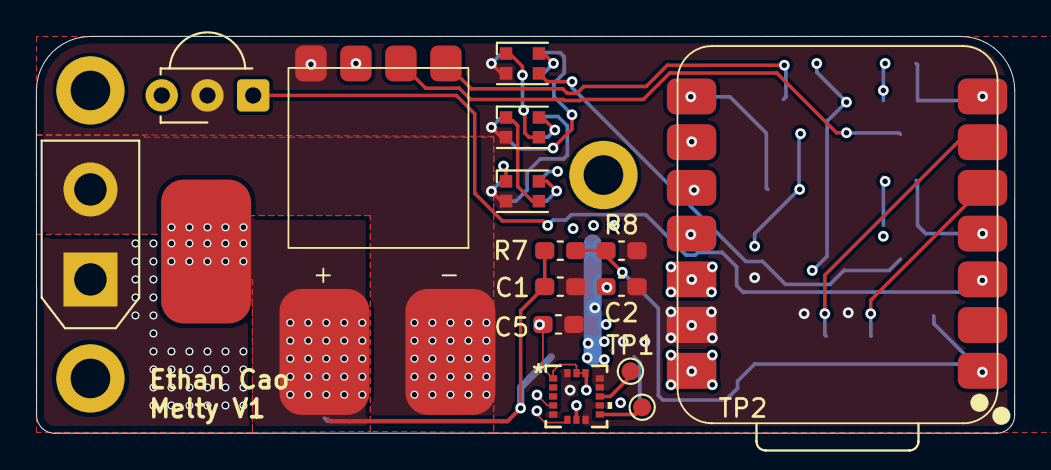
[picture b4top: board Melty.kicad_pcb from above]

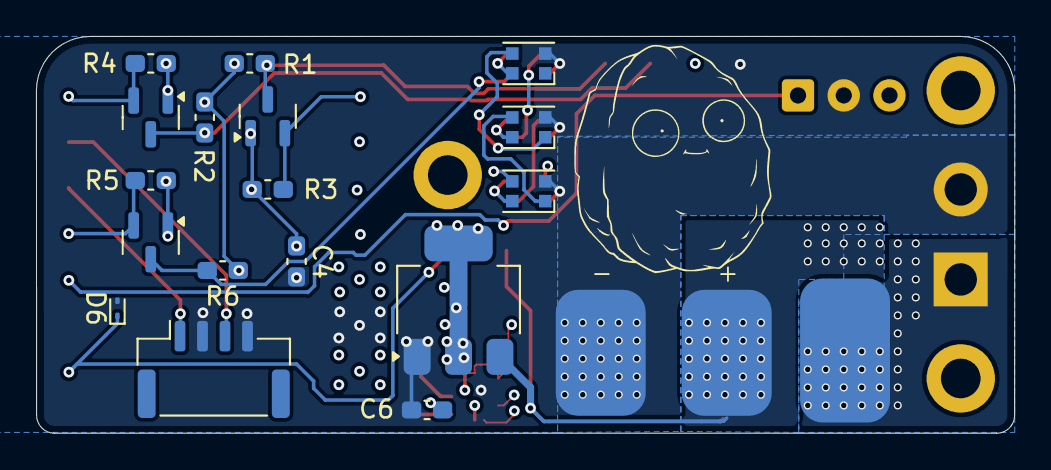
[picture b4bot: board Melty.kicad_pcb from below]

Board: 6 copper layers, 54.3 x 22.0 mm, 35 parts (18 on the bottom side), 25 nets.

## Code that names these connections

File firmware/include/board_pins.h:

/**
 * @file board_pins.h
 * @brief Eyeliner V3.1 Top Board: schematic net -> ESP32-S3 GPIO mapping.
 *
 * Source: hardware/Eyeliner_PCB_V3/Top_Board_Netlist.net (Eeschema export
 * 2026-10-14, module U2 = Seeed XIAO-ESP32-S3-SMD). XIAO pad -> GPIO numbers
 * come from the arduino-esp32 XIAO_ESP32S3 variant (D0=1 D1=2 D2=3 D3=4 D4=5
 * D5=6 D6=43 D7=44 D8=7 D9=8 D10=9); the bottom JTAG pads are fixed ESP32-S3
 * pins (MTCK=39, MTDO=40, MTDI=41, MTMS=42). Of those only MTDO is used.
 *
 * Plain #defines so they can be used in #if and overridden via build_flags.
 * Re-check this file whenever the netlist is regenerated.
 *
 *   XIAO pad  GPIO  net                 goes to
 *   D0        1     SDA                 U3/U4 IMUs, IC1 PCA9570, I2C1 conn (100R)
 *   D1        2     SCL                 same + IC2 1A (gated SK9822 clock)
 *   D2        3     INT                 U3 INT1 + U4 INT1, 4.7k (R1) to 3V3
 *   D3        4     Sense               U5 TMUX1204 common, 1k (R14) to 3V3
 *   D4        5     Vbat_Sense          VCC_HV / (20k R11 + 2k R12)
 *   D5        6     -> Receiver RX      MCU UART TX (100R R3, ESD U6)
 *   D6        43    <- Receiver TX      MCU UART RX (100R R2, ESD U6)
 *   D7        44    ESC_Telem1          ESCs1 pin 6 (100R R22, ESD U7)
 *   D8        7     Dshot1              ESCs1 pin 5 (100R R23, ESD U7)
 *   D9        8     Dshot2              ESCs1 pin 2 (100R R21, ESD U7)
 *   D10       9     ESC_Telem2          ESCs1 pin 1 (100R R20, ESD U7)
 *   MTDO      40    LEDs                IC2 2A -> Conn_LEDs1 pin 2 (SK9822 data)
 *   MTCK/MTDI/MTMS  39/41/42            unconnected
 */
#pragma once

/* ---------------------------------------------------------------------------
 * I2C bus. 1k pull-ups to VCC_3V3 (R13 SDA, R10 SCL). Devices:
 *   U3  LSM6DSV320X  0x6B  (SDO/SA0 -> 3V3)
 *   U4  LSM6DSV320X  0x6A  (SDO/SA0 -> GND)
 *   IC1 PCA9570      0x24  (4-bit I/O expander, fixed address)
 * The I2C1 connector hangs on the same bus through 100R (R15 SCL, R16 SDA).
 * No mux on this spin (TMUX154E removed).
 * ------------------------------------------------------------------------- */
#define PIN_I2C_SDA             1   // D0      net /Top_Board/SDA
#define PIN_I2C_SCL             2   // D1      net /Top_Board/SCL

/* ---------------------------------------------------------------------------
 * IMUs: two LSM6DSV320X. INT1 of both is one net with a 4.7k pull-up (R1), so
 * INT1 must be open-drain + active-low on both (wired-OR). INT2 unconnected.
 * CS is tied to 3V3 on both (I2C mode only); aux SPI pins grounded.
 * ------------------------------------------------------------------------- */
#define PIN_IMU_INT             3   // D2      net /Top_Board/INT (U3 + U4 INT1)

#define IMU_U3_I2C_ADDR         0x6B  // SDO/SA0 tied to 3V3
#define IMU_U4_I2C_ADDR         0x6A  // SDO/SA0 tied to GND

/* ---------------------------------------------------------------------------
 * PCA9570 I/O expander (IC1, 0x24). Pins are outputs on the expander, not GPIOs.
 * ------------------------------------------------------------------------- */
#define PCA9570_I2C_ADDR        0x24
#define PCA9570_BIT_LED_CLK_EN  0   // P0 -> IC2 ~1OE: LOW = SCL passed to LED clock
#define PCA9570_BIT_TEMP_SEL_A0 1   // P1 -> U5 TMUX1204 A0
#define PCA9570_BIT_TEMP_SEL_A1 2   // P2 -> U5 TMUX1204 A1
#define PCA9570_BIT_IR_EN       3   // P3 -> Q1 (BSS138) gate; HIGH = IR1 on (100R R5)

/* ---------------------------------------------------------------------------
 * ESCs (ESCs1 JST-SH 6-pin, 100R series, RCLAMP3346P ESD on U7)
 * ------------------------------------------------------------------------- */
#define PIN_DSHOT_1             7   // D8      net /Top_Board/Dshot1    -> ESCs1.5
#define PIN_DSHOT_2             8   // D9      net /Top_Board/Dshot2    -> ESCs1.2
#define PIN_ESC_TELEM_1         44  // D7      net /Top_Board/ESC_Telem1 <- ESCs1.6
#define PIN_ESC_TELEM_2         9   // D10     net /Top_Board/ESC_Telem2 <- ESCs1.1

/* ---------------------------------------------------------------------------
 * RC receiver (Receiver1, BetaFPV ELRS Lite footprint; 100R series, ESD on U6).
 * Net names are from the receiver's point of view: Receiver_TX is the
 * receiver's output, so it is the MCU's UART RX.
 * ------------------------------------------------------------------------- */
#define PIN_RECEIVER_UART_RX    43  // D6      net /Top_Board/Receiver_TX (receiver -> MCU)
#define PIN_RECEIVER_UART_TX    6   // D5      net /Top_Board/Receiver_RX (MCU -> receiver)

/* ---------------------------------------------------------------------------
 * LEDs (Conn_LEDs1 JST-SH 4-pin: GND, DATA, CLK, 5V) for an SK9822/APA102 strip.
 * Both lines go through a 74AHCT2G125 (IC2) 3V3 -> 5V level shifter.
 *   DATA: GPIO40 -> IC2 2A/2Y (always enabled, ~2OE grounded)
 *   CLK:  the I2C SCL line -> IC2 1A/1Y, enabled by PCA9570 P0 = LOW
 * So the LED clock is bit-banged on PIN_I2C_SCL with the gate open, and the
 * gate must be closed again before the bus is used for I2C.
 * ------------------------------------------------------------------------- */
#define PIN_LED_DATA            40  // MTDO    net /Top_Board/LEDs
#define PIN_LED_CLK             PIN_I2C_SCL

/* ---------------------------------------------------------------------------
 * Analog sensing (both on ADC1)
 * ------------------------------------------------------------------------- */
#define PIN_VBAT_SENSE          5   // D4      net /Top_Board/Vbat_Sense (ADC1_CH4)
#define VBAT_DIVIDER_RATIO      11.0f // (20k + 2k) / 2k

#define PIN_TEMP_SENSE          4   // D3      net /Top_Board/Sense (ADC1_CH3), 1k R14 to 3V3
#define TEMP_SENSE_PULLUP_OHMS  1000.0f
// TMUX1204 (U5) channel select via PCA9570 P1 (A0) / P2 (A1): S = 1 + A1*2 + A0
#define TEMP_MUX_CH_REF         0   // S1: 4.7k (R19) to GND, calibration reference
#define TEMP_MUX_CH_RTD_ONBOARD 1   // S2: RTD_Onboard1
#define TEMP_MUX_CH_TEMP2       2   // S3: Temps1 pin 2 (100R R17)
#define TEMP_MUX_CH_TEMP1       3   // S4: Temps1 pin 3 (100R R18)

/* ---------------------------------------------------------------------------
 * Legacy names from the V3.0 header, kept only so older sources still build.
 * None of these nets exist on V3.1; they point at unconnected JTAG pads.
 * Remove the users rather than relying on these.
 * ------------------------------------------------------------------------- */
#define PIN_RECEIVER_TX         PIN_RECEIVER_UART_RX   // old name, same net
#define PIN_RECEIVER_RX         PIN_RECEIVER_UART_TX
#define IMU_U5_I2C_ADDR         IMU_U4_I2C_ADDR        // old ref for the 0x6A part
#define PIN_I2C_SEL             41  // MTDI, unconnected (no I2C mux on V3.1)
#define I2C_SEL_LEVEL_IMU       0
#define I2C_SEL_LEVEL_EXTRA     1
#define PIN_TEMP_SEL_1          39  // MTCK, unconnected (select is on the PCA9570 now)
#define PIN_TEMP_SEL_2          42  // MTMS, unconnected

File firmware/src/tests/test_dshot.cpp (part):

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 *                  plain frame (shows crosstalk only). Prints the edge timeline.
 *   d              toggle raw hex dump of telemetry bytes (gap = new line)
 *
 * Wiring (V3.1 Top Board, Dshot2 connector by default; see DSHOT_PIN):
 *   GPIO8 (D9, net Dshot2)      -> ESC signal, 100R series + ESD on the board
 *   GPIO9 (D10, net ESC_Telem2) <- ESC TELEM pad (ESC TX, 115200 8N1)
 *   GND shared.
 * Bidirectional (one-wire eRPM) DShot needs a 1k pull-up to 3V3 on the ESC side
 * of the series resistor, which the board does not have. It is off by default;
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 * Configuration (override any of these from build_flags)
 * ------------------------------------------------------------------------- */
// Defaults are the V3.1 Top Board's Dshot2 connector (Top_Board_Netlist.net):
//   Dshot1 = D8/GPIO7 with ESC_Telem1 = D7/GPIO44
//   Dshot2 = D9/GPIO8 with ESC_Telem2 = D10/GPIO9
#ifndef DSHOT_PIN
#define DSHOT_PIN 8            // D9, net Dshot2
#endif
#ifndef DSHOT_TELEM_PIN
#define DSHOT_TELEM_PIN 9      // D10, net ESC_Telem2 (ESC -> MCU)
#endif
#ifndef DSHOT_BIDIR
#define DSHOT_BIDIR 0          // 1 = one-wire bidirectional (needs 1k pull-up)
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
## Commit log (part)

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2026-06-02 init: initial version, added v0 firmware alongside docs and cad files
2026-06-02 Should now be updated to v0
2026-06-02 v0 should actually be good now
2026-06-03 Added Latest PCB files (V0 was pretty bad lol, maybe not the best idea to include that)
2026-06-03 Updated code to last spec, refer to readme for past versions. Docs also updated
2026-06-04 Slightly updated readme page to be more concise
2026-06-04 Added portfolio link
2026-06-05 Added datasheets
